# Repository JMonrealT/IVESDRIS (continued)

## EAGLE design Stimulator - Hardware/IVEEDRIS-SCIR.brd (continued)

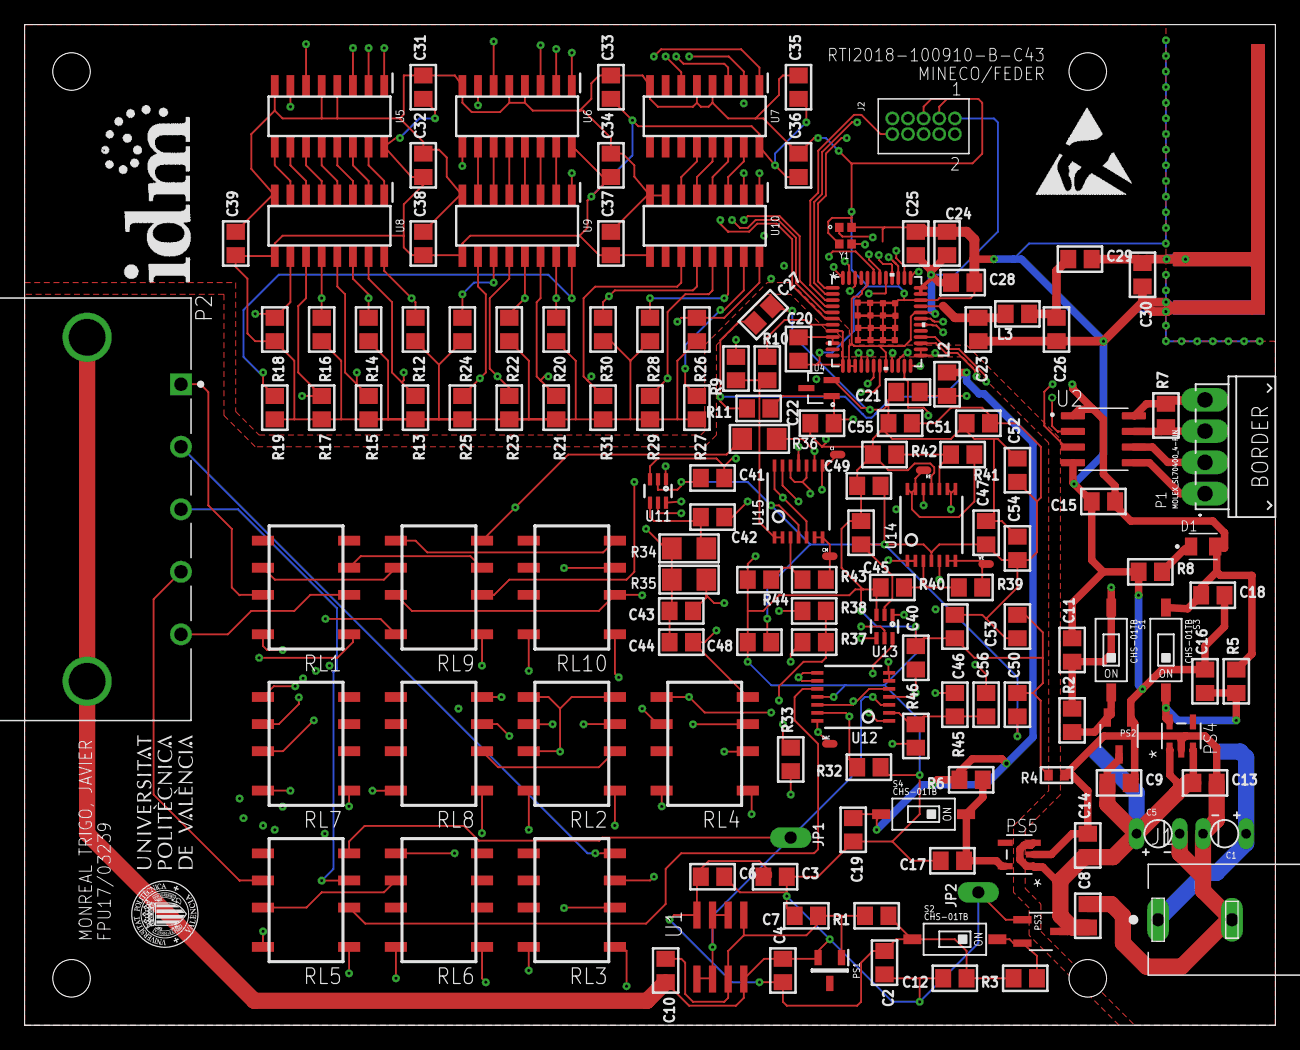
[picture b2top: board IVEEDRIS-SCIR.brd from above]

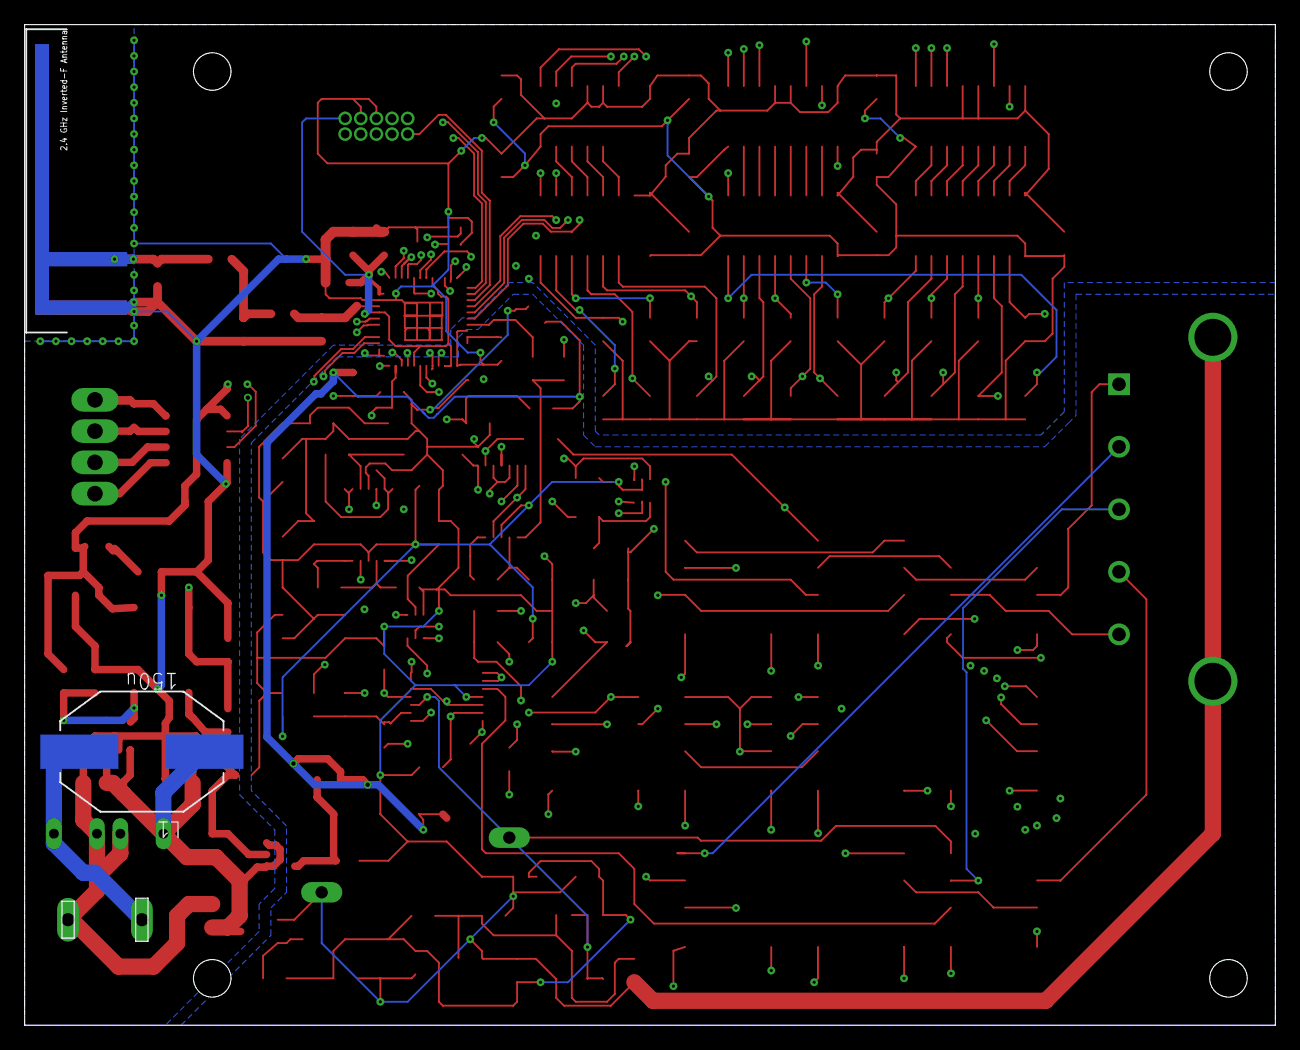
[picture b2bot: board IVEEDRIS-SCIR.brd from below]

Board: 4 copper layers, 101.6 x 81.3 mm, 153 parts (2 on the bottom side), 131 nets.

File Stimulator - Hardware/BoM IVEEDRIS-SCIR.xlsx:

Components for ASSEMBLER Eurocircuits
Qty | Value | Device | Package | Parts | Description | DIGIKEY_PRICE-STOCK | HEIGHT | MANUFACTURER_NAME | MANUFACTURER_PART_NUMBER | SUPPLIER_PART_NUMBER
1 |  | ADR5043BKSZ-REEL7KS_3_ADI-M | KS_3_ADI-M | U4 |  |  |  | Analog Devices Inc | ADR5043BKSZ-REEL7
3 |  | CAP_CERAMIC0805 | 805 | C42, C43, C44 | Ceramic Capacitors
10 |  | G6KU-2F-Y | G6KU-2F-Y | RL1, RL2, RL3, RL4, RL5, RL6, RL7, RL8, RL9, RL10 |  | https://www.digikey.com/es/products/detail/omron-electronics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 |  | Omron Electronics Inc-EMC Div | G6KU-2F-Y DC5 | Z3303-ND
1 |  | RESISTOR0402 | 402 | R4 | Resistors
1 | 0.0051uH | INDUCTOR0805 | 805 | L3 | Inductors
4 | 0.1u | CAP_CERAMIC0805 | 805 | C22, C24, C25, C27 | Ceramic Capacitors
1 | 0.1uH | INDUCTOR0805 | 805 | L2 | Inductors
2 | 0.7p | CAP_CERAMIC0805 | 805 | C23, C26 | Ceramic Capacitors
1 | 1-316130-2 | 1-316130-2 | TE_1-316130-2 | P2 | CONN HDR 5POS R/A KEY-X 15GOLD | https://www.digikey.com/es/products/detail/te-connectivity-a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 |  | TE Connectivity AMP Connectors | 1-316130-2 | A29616-ND
1 | 100k | RESISTOR1206 | 1206 | R34 | Resistors
17 | 100n | CAP_CERAMIC0805 | 805 | C2, C7, C15, C31, C33, C35, C37, C38, C39, C41, C46, C50, C51, C52, C53, C54, C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 | Ceramic Capacitors
3 | 10k | RESISTOR0805 | 805 | R1, R45, R46 | Resistors
8 | 10n | CAP_CERAMIC0805 | 805 | C4, C6, C10, C16, C17, C40, C45, C47 | Ceramic Capacitors
2 | 10p | CAP_CERAMIC0805 | 805 | C29, C30 | Ceramic Capacitors
4 | 10u | CAP_CERAMIC0805 | 805 | C3, C18, C19, C20 | Ceramic Capacitors
1 | 120 | RESISTOR0805 | 805 | R7 | Resistors
1 | 12k | RESISTOR1206 | 1206 | R36 | Resistors
1 | 12p | CAP_CERAMIC0805 | 805 | C28 | Ceramic Capacitors
2 | 18k | RESISTOR0805 | 805 | R39, R43 | Resistors
1 | 18k | RESISTOR0805 | 805 | R41 | Resistors
1 | 1k | RESISTOR1206 | 1206 | R35 | Resistors
2 | 1m | APSG160ELL102MH20S | CAP_ALUMINIUM | C1, C5 |  | https://www.digikey.com/es/products/detail/united-chemi-con/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 |  | United Chemi-Con | APSG160ELL102MH20S | 565-4311-ND
12 | 1u | CAP_CERAMIC0805 | 805 | C8, C9, C11, C12, C13, C14, C21, C32, C34, C36, C48, C49 | Ceramic Capacitors
1 | 20k | RESISTOR0805 | 805 | R33 | Resistors
1 | 220 | RESISTOR0805 | 805 | R8 | Resistors
1 | 22p | CAP_CERAMIC0805 | 805 | C56 | Ceramic Capacitors
3 | 27k | RESISTOR0805 | 805 | R40, R42, R44 | Resistors
1 | 30k | RESISTOR0805 | 805 | R32 | Resistors
20 | 50 | RESISTOR0805 | 805 | R12, R13, R14, R15, R16, R17, R18, R19, R20, R21, R22, R23, R24, R25, R26, R27,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 | Resistors
3 | 74HCT238D | 74HCT238D | SOIC127P600X175-16N | U5, U6, U7 | 74HCT238D, Decoder, Demultiplexer HCT, 1-of-8 Non-Inverting 5V 16-Pin SOIC | https://www.digikey.com/es/products/detail/nexperia-usa-inc/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 | 1.75mm | Nexperia | 74HCT238D,652 | 1727-3389-ND
1 | 820 | RESISTOR0805 | 805 | R11 | Resistors
2 | ADG839 | ADG839 | SC70-6L | U11, U13 | Analog switch. | https://www.digikey.com/es/products/detail/analog-devices-in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 |  | Analog Devices Inc. | ADG839YKSZ-500RL7 | ADG839YKSZ-500RL7TR-ND
4 | CHS-01TB | CHS-01TB | CHS-01TB | S1, S2, S3, S4 |  | https://www.digikey.com/es/products/detail/nidec-copal-elect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 |  | Nidec Copal Electronics | CHS-01TB | 563-1004-2-ND
1 | FTSH-105-XX-XX-D | FTSH-105-XX-XX-D | FTSH-105-XX-XX-D | J2 | 0.050X0.050" CL THROUGH HOLE TERMINAL STRIP ASSEMBLY,10 PINS." | https://www.digikey.com/es/products/detail/samtec-inc/FTSH-1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 |  | Samtec | FTSH-105-04-F-D | SAM9443-ND
1 | LM4040DEM3-2.5_NOPB | LM4040DEM3-2.5_NOPB | SOT95P237X112-3N | PS1 |  | https://www.digikey.com/es/products/detail/texas-instruments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 |  | Texas Instruments | LM4040DEM3X-2.5/NOPB | 296-LM4040DEM3X-2.5/NOPBTR-ND
2 | LT1761ES5-3.3TRPBF | LT1761ES5-3.3TRPBF | TSOT-23_S5 | PS4, PS5 |  | https://www.digikey.com/es/products/detail/analog-devices-in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 |  | Linear Technologies | lt1761es5-3.3#trpbf | LT1761ES5-3.3#TRPBFTR-ND
1 | MAX3490ECSA+ | MAX3490ECSA+ | SOIC127P600X175-8N | U2 | Interface IC - transceivers Maxim Integrated MAX3490ECSA+ RS422, RS485 1/1 SOIC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 | https://www.digikey.com/es/products/detail/maxim-integrated/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 |  | Maxim Integrated | MAX3490ECSA+ | MAX3490ECSA+TTR-ND
2 | MCP1702 | MCP1702 | SOT23-A | PS2, PS3 |  | https://www.digikey.com/es/products/detail/microchip-technol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 |  | Microchip Technology | MCP1702T-2502E/CB | MCP1702T-2502E/CBTR-ND
1 | MKW41Z512VHT4 | MKW41Z512VHT4 | LQFN48_7X7 | U3 |  | https://www.digikey.com/es/products/detail/nxp-usa-inc/MKW41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 |  | NXP | mkw41z512vht4 | MKW41Z512VHT4-ND
1 | MOLEX_SL70400_4-PIN | MOLEX_SL70400_4-PIN | MOLEX_SL70400_4-PIN | P1 |  | https://www.digikey.es/product-detail/es/molex/0705530038/WM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 |  | Molex | 705530038 | WM4926-ND
3 | OPA4376PW | OPA4376PW | TSSOP14-NOTHERMALPAD | U12, U14, U15
1 | PJ-037A | PJ-037A | CUI_PJ-037A | J1 | 2.0 mm Center Pin, 2.5 A, Right Angle, Through Hole, Dc Power Jack Connector Ch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 | https://www.digikey.es/product-detail/es/cui-devices/PJ-037A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 |  | CUI Devices | PJ-037A | CP-037A-ND
1 | SM0805UGC | SM0805UGC | LEDC2012X135N | D1 | LED; SMD; 0805; Ultra Green; 563nm; 10mcd; Water Clear Lens; 130 Deg Viewing An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 | https://www.digikey.es/product-detail/es/bivar-inc/SM0805UGC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 |  | Bivar Inc. | SM0805UGC | 492-1329-1-ND
1 | TLV2462IDG4 | TLV2462IDG4 | SO8 | U1 |  | https://www.digikey.es/product-detail/es/texas-instruments/T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 |  | Texas Instruments | TLV2462AQDRQ1 | 296-17738-1-ND
3 | ULN2003LVDR | ULN2003LVDR | SOIC127P600X175-16N | U8, U9, U10 | 7-Ch Relay, Inductive Sink Driver SOIC16 Texas Instruments ULN2003LVDR, 7-eleme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 | https://www.digikey.es/product-detail/es/texas-instruments/U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 | 1.75mm | Texas Instruments | ULN2003LVDR | 296-30403-1-ND
1 | XRCGB32M000FBH50R0 | XRCGB32M000FBH50R0 | XRCGB32_F | Y1 | MURATA - XRCGB32M000FBH50R0 - CRYSTAL, 32MHZ, 10PF, SMD, 2MM X 1.6MM | https://www.digikey.es/product-detail/es/murata-electronics/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 |  | Murata Electronics | XRCGB32M000FBH50R0 | 490-18345-1-ND

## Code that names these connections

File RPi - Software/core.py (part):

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# Hardware init function
def hwInit():
    # Configure GPIO for controlling both UART-RS interfaces
    # RE_M! 11 | GPIO 0          |
    # RE_S! 13 | GPIO 2          |
    # DE_M  15 | GPIO 3   GPIO 4 | 16 DE_S
    gpio.setwarnings(False)
    gpio.setmode(gpio.BOARD) 
    gpio.setup(11, gpio.OUT)
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# Select communication between IVEEDRIS and MS
def selectCommunication(dest): # dest = ('IVEEDRIS','MS')
    # Configure GPIO for controlling both UART-RS interfaces
    # RE_M! 11 | GPIO 0          |
    # RE_S! 13 | GPIO 2          |
    # DE_M  15 | GPIO 3   GPIO 4 | 16 DE_S
    s = getObjectSerial()
    if dest == 'IVEEDRIS':
        s.baudrate = 1843200
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
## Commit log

2023-02-21 CC BY-NC-SA LICENSE
    CC BY-NC-SA
    This license allows reusers to distribute, remix, adapt, and build upon the material in any medium or format for noncommercial purposes only, and only so long as attribution is given to the creator. 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
    For commercial permissions contact: jmonreal@upv.es
2024-09-23 Files added
